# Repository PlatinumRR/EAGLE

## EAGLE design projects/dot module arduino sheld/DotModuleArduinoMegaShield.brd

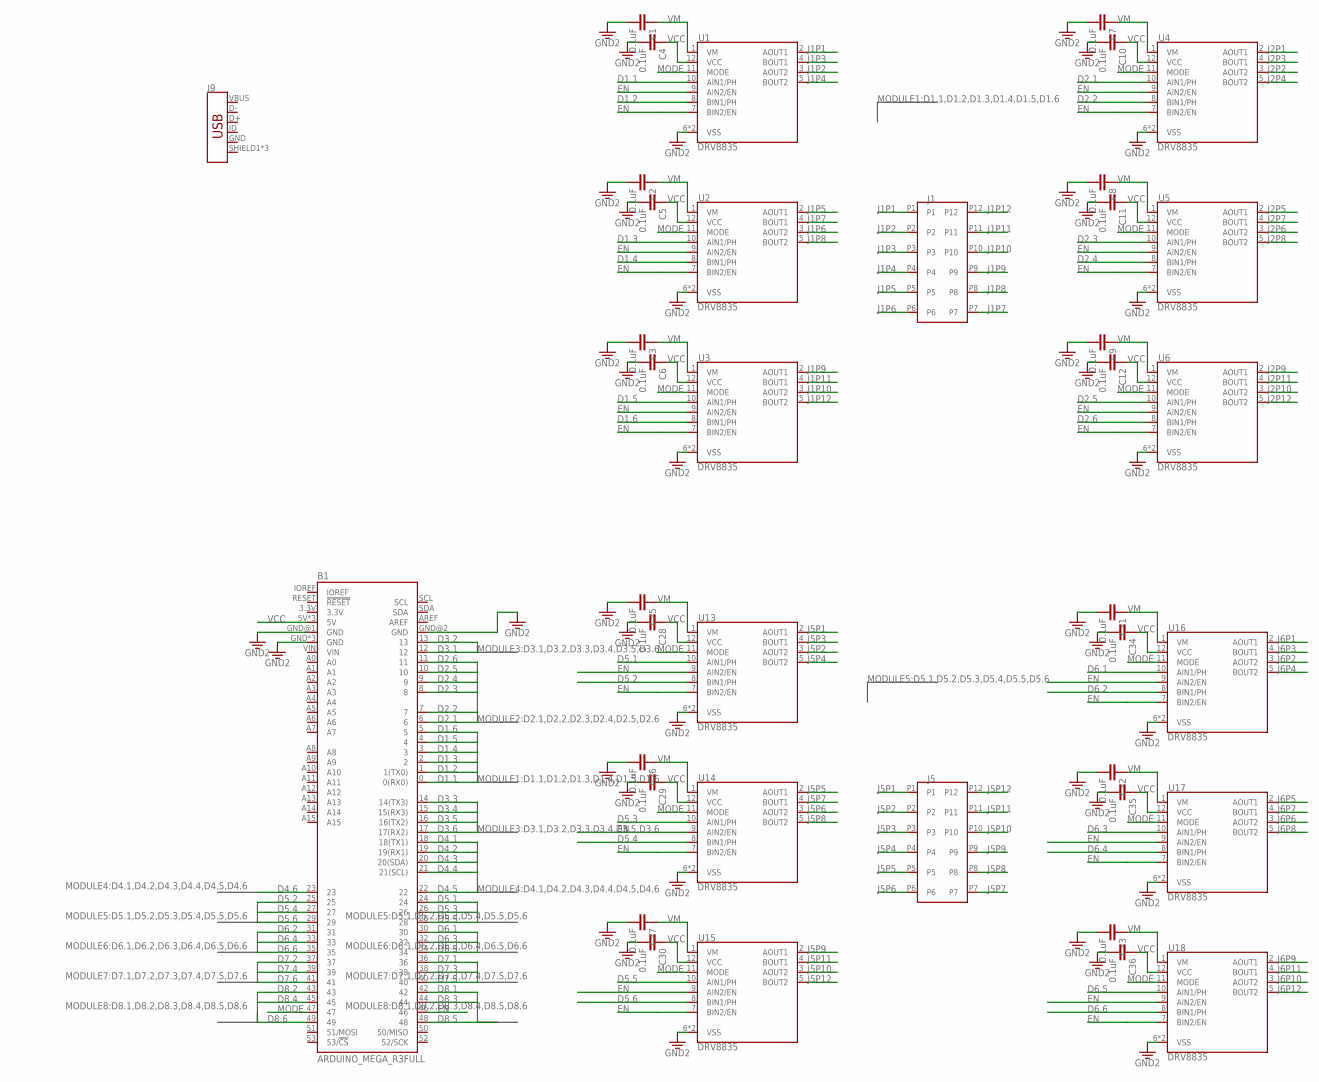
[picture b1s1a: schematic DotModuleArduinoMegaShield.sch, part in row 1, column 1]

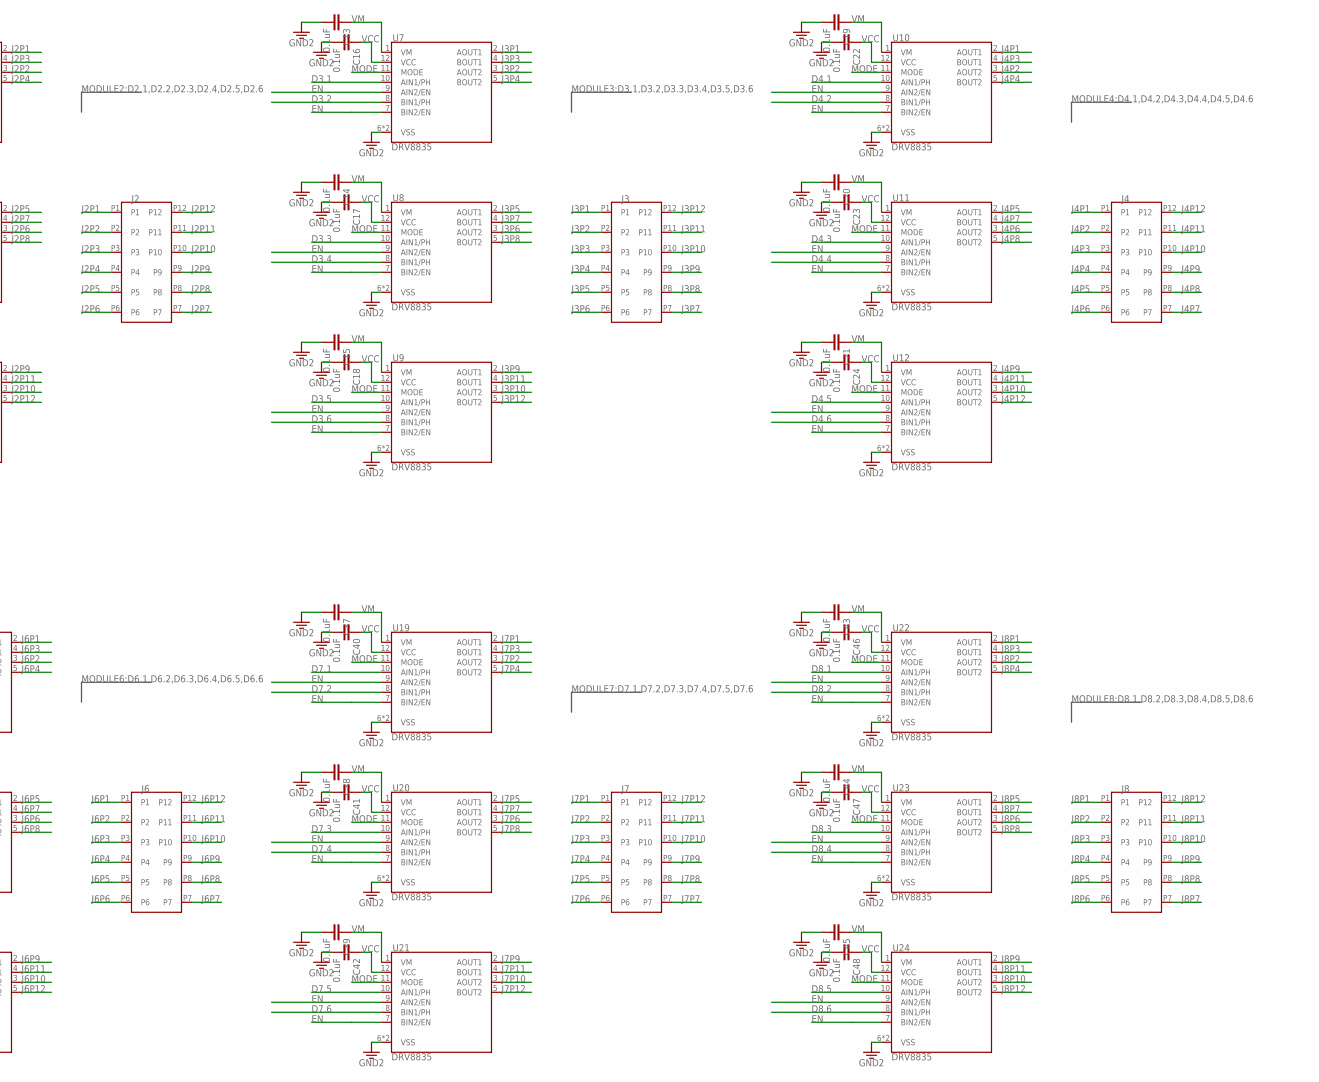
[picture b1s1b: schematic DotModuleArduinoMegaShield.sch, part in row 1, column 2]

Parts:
B1: ARDUINO_MEGA_R3FULL; ARDUINO_MEGA_NO_SILK
C1, C2, C3, C4, C5, C6, C7, C8, C9, C10, C11, C12, C13, C14, C15, C16, C17, C18, C19, C20, C21, C22, C23, C24, C25, C26, C27, C28, C29, C30, C31, C32, C33, C34, C35, C36, C37, C38, C39, C40, C41, C42, C43, C44, C45, C46, C47, C48: 0.1uF; 0402
J1, J2, J3, J4, J5, J6, J7, J8: AXE612124-12PIN
J9: USB_MICRO-BREDUCED_PASTE; USB-B-MICRO-SMD_RED_PASTE
U1, U2, U3, U4, U5, U6, U7, U8, U9, U10, U11, U12, U13, U14, U15, U16, U17, U18, U19, U20, U21, U22, U23, U24: DRV8835; WSON-12

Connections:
3.3V: B1.GND@2 (GND)
D1.1: B1.0 (0(RX0)), U1.10 (AIN1/PH)
D1.2: B1.1 (1(TX0)), U1.8 (BIN1/PH)
D1.3: B1.2, U2.10 (AIN1/PH)
D1.4: B1.3, U2.8 (BIN1/PH)
D1.5: B1.4, U3.10 (AIN1/PH)
D1.6: B1.5, U3.8 (BIN1/PH)
D2.1: B1.6, U4.10 (AIN1/PH)
D2.2: B1.7, U4.8 (BIN1/PH)
D2.3: B1.8, U5.10 (AIN1/PH)
D2.4: B1.9, U5.8 (BIN1/PH)
D2.5: B1.10, U6.10 (AIN1/PH)
D2.6: B1.11, U6.8 (BIN1/PH)
D3.1: B1.12, U7.10 (AIN1/PH)
D3.2: B1.13, U7.8 (BIN1/PH)
D3.3: B1.14 (14(TX3)), U8.10 (AIN1/PH)
D3.4: B1.15 (15(RX3)), U8.8 (BIN1/PH)
D3.5: B1.16 (16(TX2)), U9.10 (AIN1/PH)
D3.6: B1.17 (17(RX2)), U9.8 (BIN1/PH)
D4.1: B1.18 (18(TX1)), U10.10 (AIN1/PH)
D4.2: B1.19 (19(RX1)), U10.8 (BIN1/PH)
D4.3: B1.20 (20(SDA)), U11.10 (AIN1/PH)
D4.4: B1.21 (21(SCL)), U11.8 (BIN1/PH)
D4.5: B1.22, U12.10 (AIN1/PH)
D4.6: B1.23, U12.8 (BIN1/PH)
D5.1: B1.24, U13.10 (AIN1/PH)
D5.2: B1.25, U13.8 (BIN1/PH)
D5.3: B1.26, U14.10 (AIN1/PH)
D5.4: B1.27, U14.8 (BIN1/PH)
D5.5: B1.28, U15.10 (AIN1/PH)
D5.6: B1.29, U15.8 (BIN1/PH)
D6.1: B1.30, U16.10 (AIN1/PH)
D6.2: B1.31, U16.8 (BIN1/PH)
D6.3: B1.32, U17.10 (AIN1/PH)
D6.4: B1.33, U17.8 (BIN1/PH)
D6.5: B1.34, U18.10 (AIN1/PH)
D6.6: B1.35, U18.8 (BIN1/PH)
D7.1: B1.36, U19.10 (AIN1/PH)
D7.2: B1.37, U19.8 (BIN1/PH)
D7.3: B1.38, U20.10 (AIN1/PH)
D7.4: B1.39, U20.8 (BIN1/PH)
D7.5: B1.40, U21.10 (AIN1/PH)
D7.6: B1.41, U21.8 (BIN1/PH)
D8.1: B1.42, U22.10 (AIN1/PH)
D8.2: B1.43, U22.8 (BIN1/PH)
D8.3: B1.44, U23.10 (AIN1/PH)
D8.4: B1.45, U23.8 (BIN1/PH)
D8.5: B1.48, U24.10 (AIN1/PH)
D8.6: B1.49, U24.8 (BIN1/PH)
EN: B1.46, U1.7 (BIN2/EN), U1.9 (AIN2/EN), U2.7 (BIN2/EN), U2.9 (AIN2/EN), U3.7 (BIN2/EN), U3.9 (AIN2/EN), U4.7 (BIN2/EN), U4.9 (AIN2/EN), U5.7 (BIN2/EN), U5.9 (AIN2/EN), U6.7 (BIN2/EN), U6.9 (AIN2/EN), U7.7 (BIN2/EN), U7.9 (AIN2/EN), U8.7 (BIN2/EN), U8.9 (AIN2/EN), U9.7 (BIN2/EN), U9.9 (AIN2/EN), U10.7 (BIN2/EN), U10.9 (AIN2/EN), U11.7 (BIN2/EN), U11.9 (AIN2/EN), U12.7 (BIN2/EN), U12.9 (AIN2/EN), U13.7 (BIN2/EN), U13.9 (AIN2/EN), U14.7 (BIN2/EN), U14.9 (AIN2/EN), U15.7 (BIN2/EN), U15.9 (AIN2/EN), U16.7 (BIN2/EN), U16.9 (AIN2/EN), U17.7 (BIN2/EN), U17.9 (AIN2/EN), U18.7 (BIN2/EN), U18.9 (AIN2/EN), U19.7 (BIN2/EN), U19.9 (AIN2/EN), U20.7 (BIN2/EN), U20.9 (AIN2/EN), U21.7 (BIN2/EN), U21.9 (AIN2/EN), U22.7 (BIN2/EN), U22.9 (AIN2/EN), U23.7 (BIN2/EN), U23.9 (AIN2/EN), U24.7 (BIN2/EN), U24.9 (AIN2/EN)
GND: B1.GND, B1.GND@1 (GND), B1.GND@3 (GND), B1.GND@4 (GND), C1.2, C2.2, C3.2, C4.2, C5.2, C6.2, C7.2, C8.2, C9.2, C10.2, C11.2, C12.2, C13.2, C14.2, C15.2, C16.2, C17.2, C18.2, C19.2, C20.2, C21.2, C22.2, C23.2, C24.2, C25.2, C26.2, C27.2, C28.2, C29.2, C30.2, C31.2, C32.2, C33.2, C34.2, C35.2, C36.2, C37.2, C38.2, C39.2, C40.2, C41.2, C42.2, C43.2, C44.2, C45.2, C46.2, C47.2, C48.2, J9.GND, U1.6 (VSS), U1.PAD (VSS), U2.6 (VSS), U2.PAD (VSS), U3.6 (VSS), U3.PAD (VSS), U4.6 (VSS), U4.PAD (VSS), U5.6 (VSS), U5.PAD (VSS), U6.6 (VSS), U6.PAD (VSS), U7.6 (VSS), U7.PAD (VSS), U8.6 (VSS), U8.PAD (VSS), U9.6 (VSS), U9.PAD (VSS), U10.6 (VSS), U10.PAD (VSS), U11.6 (VSS), U11.PAD (VSS), U12.6 (VSS), U12.PAD (VSS), U13.6 (VSS), U13.PAD (VSS), U14.6 (VSS), U14.PAD (VSS), U15.6 (VSS), U15.PAD (VSS), U16.6 (VSS), U16.PAD (VSS), U17.6 (VSS), U17.PAD (VSS), U18.6 (VSS), U18.PAD (VSS), U19.6 (VSS), U19.PAD (VSS), U20.6 (VSS), U20.PAD (VSS), U21.6 (VSS), U21.PAD (VSS), U22.6 (VSS), U22.PAD (VSS), U23.6 (VSS), U23.PAD (VSS), U24.6 (VSS), U24.PAD (VSS)
J1P1: J1.P1, U1.2 (AOUT1)
J1P2: J1.P2, U1.3 (AOUT2)
J1P3: J1.P3, U1.4 (BOUT1)
J1P4: J1.P4, U1.5 (BOUT2)
J1P5: J1.P5, U2.2 (AOUT1)
J1P6: J1.P6, U2.3 (AOUT2)
J1P7: J1.P7, U2.4 (BOUT1)
J1P8: J1.P8, U2.5 (BOUT2)
J1P9: J1.P9, U3.2 (AOUT1)
J1P10: J1.P10, U3.3 (AOUT2)
J1P11: J1.P11, U3.4 (BOUT1)
J1P12: J1.P12, U3.5 (BOUT2)
J2P1: J2.P1, U4.2 (AOUT1)
J2P2: J2.P2, U4.3 (AOUT2)
J2P3: J2.P3, U4.4 (BOUT1)
J2P4: J2.P4, U4.5 (BOUT2)
J2P5: J2.P5, U5.2 (AOUT1)
J2P6: J2.P6, U5.3 (AOUT2)
J2P7: J2.P7, U5.4 (BOUT1)
J2P8: J2.P8, U5.5 (BOUT2)
J2P9: J2.P9, U6.2 (AOUT1)
J2P10: J2.P10, U6.3 (AOUT2)
J2P11: J2.P11, U6.4 (BOUT1)
J2P12: J2.P12, U6.5 (BOUT2)
J3P1: J3.P1, U7.2 (AOUT1)
J3P2: J3.P2, U7.3 (AOUT2)
J3P3: J3.P3, U7.4 (BOUT1)
J3P4: J3.P4, U7.5 (BOUT2)
J3P5: J3.P5, U8.2 (AOUT1)
J3P6: J3.P6, U8.3 (AOUT2)
J3P7: J3.P7, U8.4 (BOUT1)
J3P8: J3.P8, U8.5 (BOUT2)
J3P9: J3.P9, U9.2 (AOUT1)
J3P10: J3.P10, U9.3 (AOUT2)
J3P11: J3.P11, U9.4 (BOUT1)
J3P12: J3.P12, U9.5 (BOUT2)
J4P1: J4.P1, U10.2 (AOUT1)
J4P2: J4.P2, U10.3 (AOUT2)
J4P3: J4.P3, U10.4 (BOUT1)
J4P4: J4.P4, U10.5 (BOUT2)
J4P5: J4.P5, U11.2 (AOUT1)
J4P6: J4.P6, U11.3 (AOUT2)
J4P7: J4.P7, U11.4 (BOUT1)
J4P8: J4.P8, U11.5 (BOUT2)
J4P9: J4.P9, U12.2 (AOUT1)
J4P10: J4.P10, U12.3 (AOUT2)
J4P11: J4.P11, U12.4 (BOUT1)
J4P12: J4.P12, U12.5 (BOUT2)
J5P1: J5.P1, U13.2 (AOUT1)
J5P2: J5.P2, U13.3 (AOUT2)
J5P3: J5.P3, U13.4 (BOUT1)
J5P4: J5.P4, U13.5 (BOUT2)
J5P5: J5.P5, U14.2 (AOUT1)
J5P6: J5.P6, U14.3 (AOUT2)
J5P7: J5.P7, U14.4 (BOUT1)
J5P8: J5.P8, U14.5 (BOUT2)
J5P9: J5.P9, U15.2 (AOUT1)
J5P10: J5.P10, U15.3 (AOUT2)
J5P11: J5.P11, U15.4 (BOUT1)
J5P12: J5.P12, U15.5 (BOUT2)
J6P1: J6.P1, U16.2 (AOUT1)
J6P2: J6.P2, U16.3 (AOUT2)
J6P3: J6.P3, U16.4 (BOUT1)
J6P4: J6.P4, U16.5 (BOUT2)
J6P5: J6.P5, U17.2 (AOUT1)
J6P6: J6.P6, U17.3 (AOUT2)
J6P7: J6.P7, U17.4 (BOUT1)
J6P8: J6.P8, U17.5 (BOUT2)
J6P9: J6.P9, U18.2 (AOUT1)
J6P10: J6.P10, U18.3 (AOUT2)
J6P11: J6.P11, U18.4 (BOUT1)
J6P12: J6.P12, U18.5 (BOUT2)
J7P1: J7.P1, U19.2 (AOUT1)
J7P2: J7.P2, U19.3 (AOUT2)
J7P3: J7.P3, U19.4 (BOUT1)
J7P4: J7.P4, U19.5 (BOUT2)
J7P5: J7.P5, U20.2 (AOUT1)
J7P6: J7.P6, U20.3 (AOUT2)
J7P7: J7.P7, U20.4 (BOUT1)
J7P8: J7.P8, U20.5 (BOUT2)
J7P9: J7.P9, U21.2 (AOUT1)
J7P10: J7.P10, U21.3 (AOUT2)
J7P11: J7.P11, U21.4 (BOUT1)
J7P12: J7.P12, U21.5 (BOUT2)
J8P1: J8.P1, U22.2 (AOUT1)
J8P2: J8.P2, U22.3 (AOUT2)
J8P3: J8.P3, U22.4 (BOUT1)
J8P4: J8.P4, U22.5 (BOUT2)
J8P5: J8.P5, U23.2 (AOUT1)
J8P6: J8.P6, U23.3 (AOUT2)
J8P7: J8.P7, U23.4 (BOUT1)
J8P8: J8.P8, U23.5 (BOUT2)
J8P9: J8.P9, U24.2 (AOUT1)
J8P10: J8.P10, U24.3 (AOUT2)
J8P11: J8.P11, U24.4 (BOUT1)
J8P12: J8.P12, U24.5 (BOUT2)
MODE: B1.47, U1.11 (MODE), U2.11 (MODE), U3.11 (MODE), U4.11 (MODE), U5.11 (MODE), U6.11 (MODE), U7.11 (MODE), U8.11 (MODE), U9.11 (MODE), U10.11 (MODE), U11.11 (MODE), U12.11 (MODE), U13.11 (MODE), U14.11 (MODE), U15.11 (MODE), U16.11 (MODE), U17.11 (MODE), U18.11 (MODE), U19.11 (MODE), U20.11 (MODE), U21.11 (MODE), U22.11 (MODE), U23.11 (MODE), U24.11 (MODE)
VBUS: J9.VBUS
VCC: B1.5V, B1.5V@1 (5V), B1.5V@2 (5V), C4.1, C5.1, C6.1, C10.1, C11.1, C12.1, C16.1, C17.1, C18.1, C22.1, C23.1, C24.1, C28.1, C29.1, C30.1, C34.1, C35.1, C36.1, C40.1, C41.1, C42.1, C46.1, C47.1, C48.1, U1.12 (VCC), U2.12 (VCC), U3.12 (VCC), U4.12 (VCC), U5.12 (VCC), U6.12 (VCC), U7.12 (VCC), U8.12 (VCC), U9.12 (VCC), U10.12 (VCC), U11.12 (VCC), U12.12 (VCC), U13.12 (VCC), U14.12 (VCC), U15.12 (VCC), U16.12 (VCC), U17.12 (VCC), U18.12 (VCC), U19.12 (VCC), U20.12 (VCC), U21.12 (VCC), U22.12 (VCC), U23.12 (VCC), U24.12 (VCC)
VM: C1.1, C2.1, C3.1, C7.1, C8.1, C9.1, C13.1, C14.1, C15.1, C19.1, C20.1, C21.1, C25.1, C26.1, C27.1, C31.1, C32.1, C33.1, C37.1, C38.1, C39.1, C43.1, C44.1, C45.1, U1.1 (VM), U2.1 (VM), U3.1 (VM), U4.1 (VM), U5.1 (VM), U6.1 (VM), U7.1 (VM), U8.1 (VM), U9.1 (VM), U10.1 (VM), U11.1 (VM), U12.1 (VM), U13.1 (VM), U14.1 (VM), U15.1 (VM), U16.1 (VM), U17.1 (VM), U18.1 (VM), U19.1 (VM), U20.1 (VM), U21.1 (VM), U22.1 (VM), U23.1 (VM), U24.1 (VM)

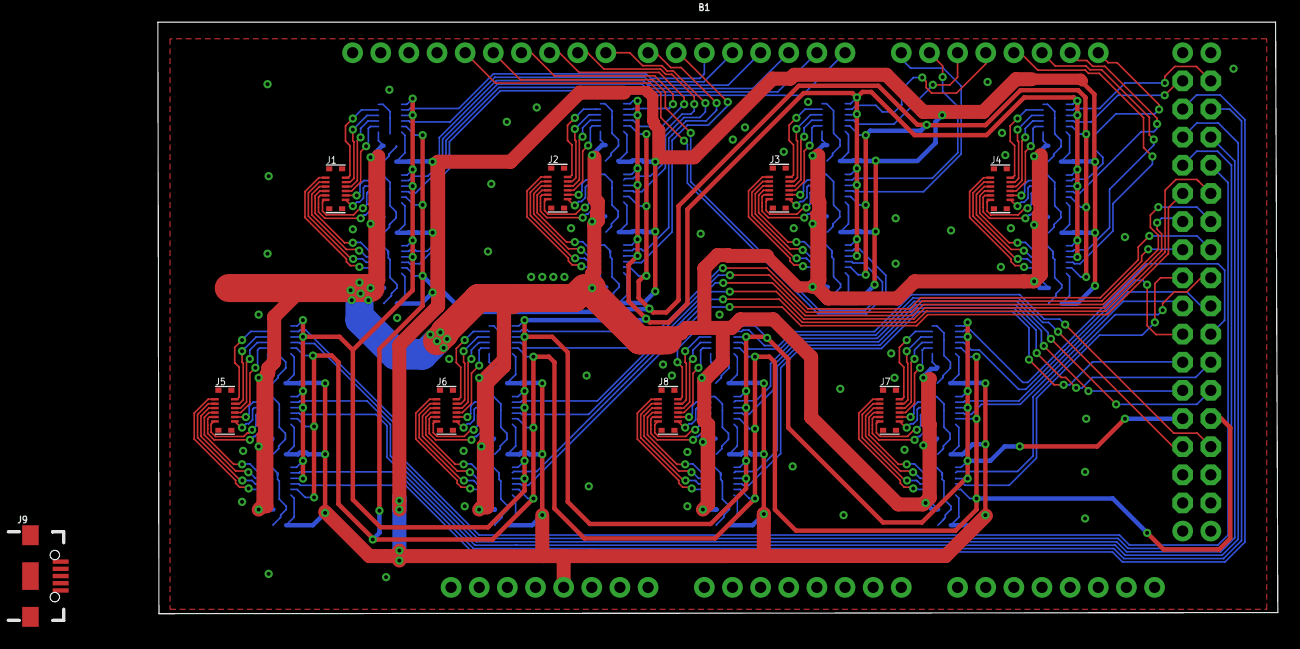
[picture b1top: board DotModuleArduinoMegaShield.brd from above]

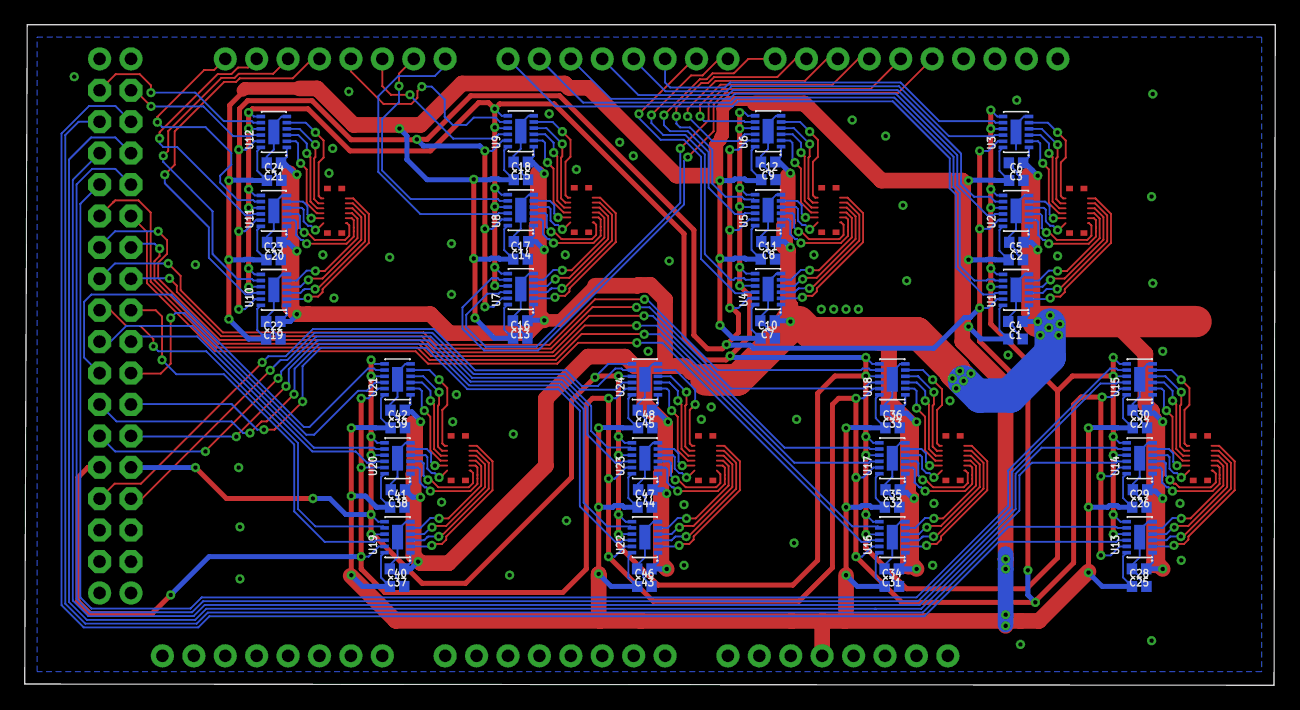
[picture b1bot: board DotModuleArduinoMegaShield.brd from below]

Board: 2 copper layers, 101.1 x 53.4 mm, 82 parts (72 on the bottom side), 149 nets.

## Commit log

2018-11-29 fist commit

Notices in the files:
parts and their libraries:
SparkFun-Boards: Licensing: Creative Commons ShareAlike 4.0 International - https://creativecommons.org/licenses/by-sa/4.0
